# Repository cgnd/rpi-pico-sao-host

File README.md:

---
typora-copy-images-to: ./images
---

# Raspberry Pi Pico SAO Host

The [Raspberry Pi Pico SAO Host](https://github.com/cgnd/rpi-pico-sao-host) is a breakout board that adds [Simple Add-on (SAO)](https://hackaday.io/project/175182-simple-add-ons-sao) host connectors to the [Raspberry Pi Pico](https://www.raspberrypi.com/products/raspberry-pi-pico/).

## v2 Design (latest)

The `v2` design adds the following features:

* A power switch (`SW2`) attached to the the Pico's `3V3_EN` input pin.
* A power LED (`D1`) that turns on when the Pico is powered on.
* A tactile reset switch (`SW1`) connected to the Pico's `RUN` input pin.

See the [CHANGELOG](CHANGELOG.md) for a full list of the changes from the previous version.

**Top (Primary) Side**

**Bottom (Secondary) Side**

### Checking out the design

To check out the design, [download the zip](https://github.com/cgnd/rpi-pico-sao-host/archive/refs/heads/v2.zip) or clone the repository using Git.

```sh
git clone https://github.com/cgnd/rpi-pico-sao-host.git
```

Open the the [RPi_Pico_SAO_Host.kicad_pro](RPi_Pico_SAO_Host.kicad_pro) project file in KiCad (requires version 9 or later).

## v1 Design

See the [README](https://github.com/cgnd/rpi-pico-sao-host/blob/v1/README.md) on the [v1](https://github.com/cgnd/rpi-pico-sao-host/tree/v1) branch for information about the `v1` design.

## License

See the [LICENSE](LICENSE.md) file for copyright & license information.

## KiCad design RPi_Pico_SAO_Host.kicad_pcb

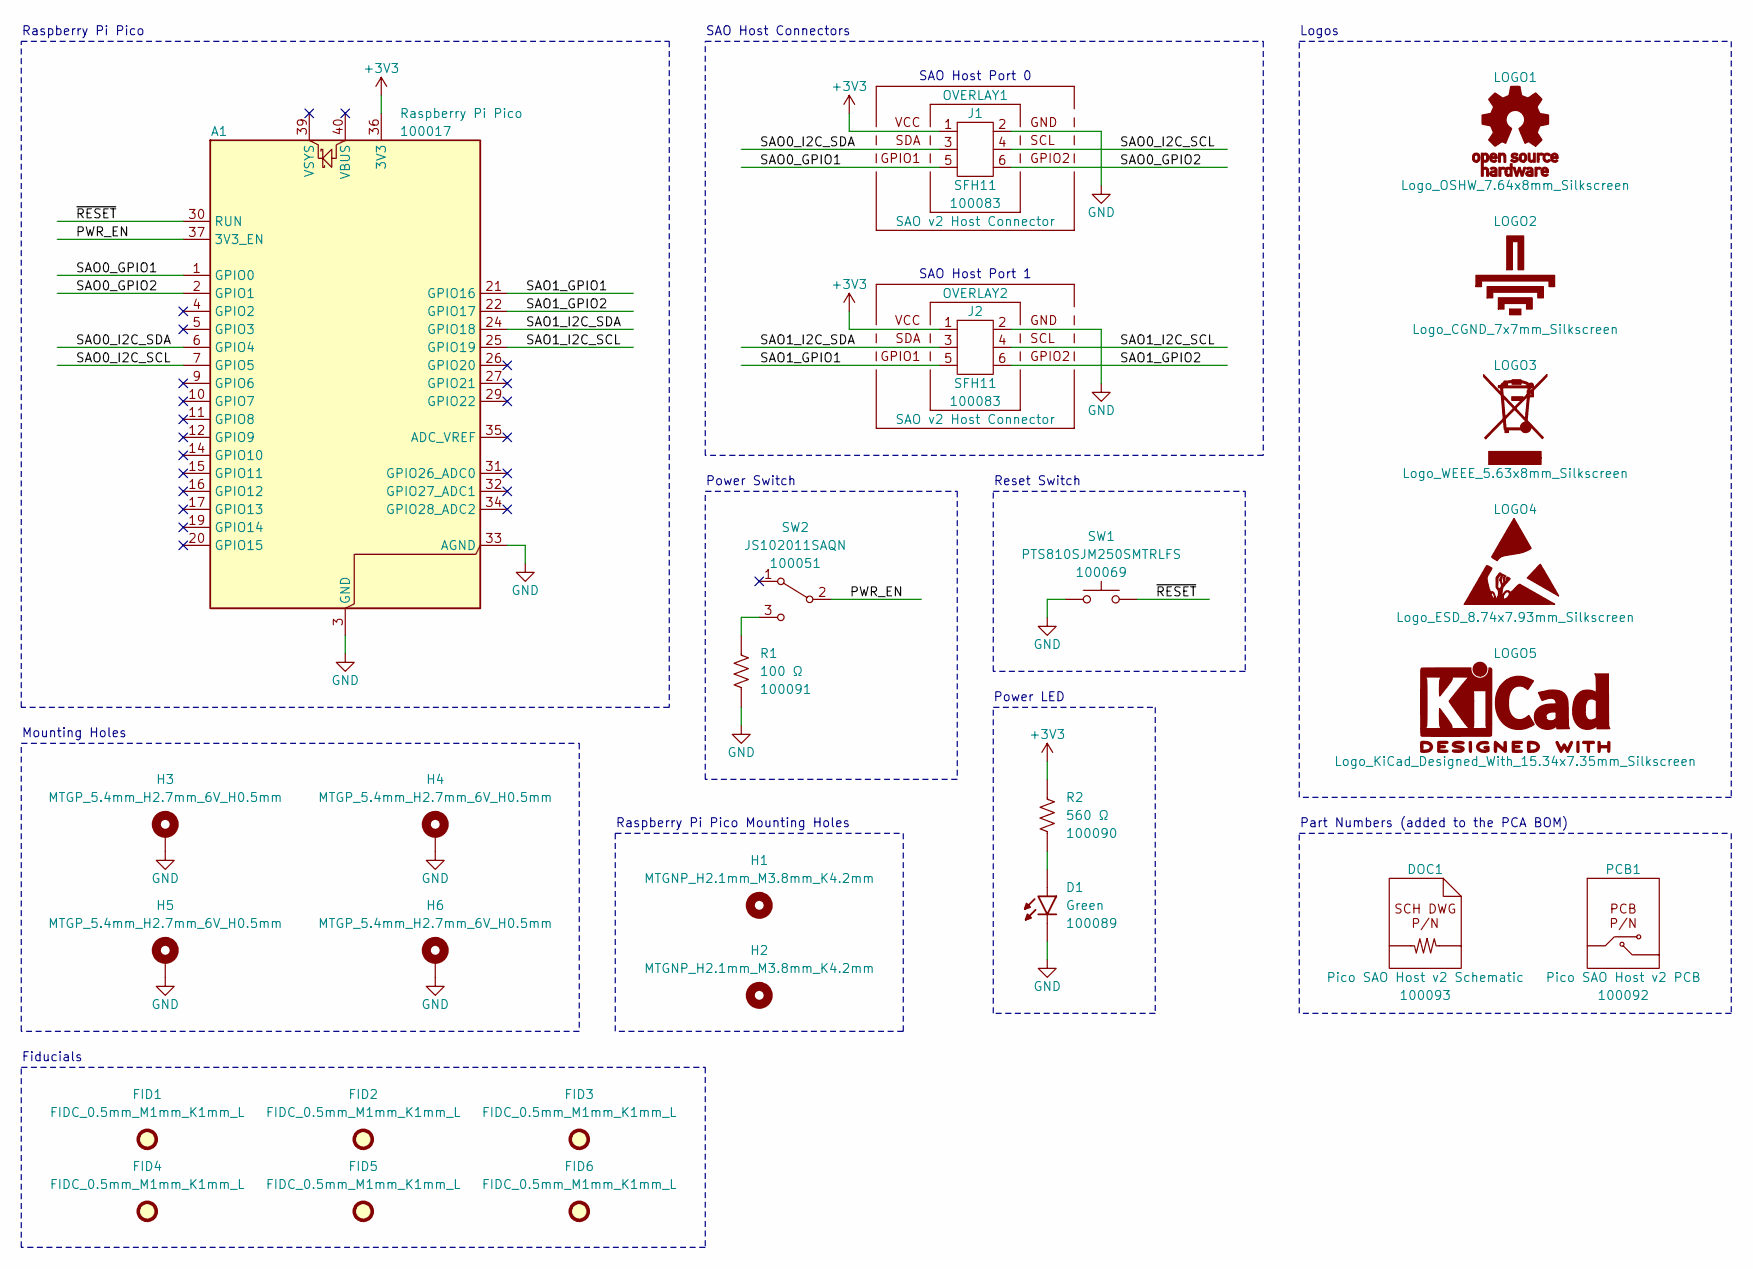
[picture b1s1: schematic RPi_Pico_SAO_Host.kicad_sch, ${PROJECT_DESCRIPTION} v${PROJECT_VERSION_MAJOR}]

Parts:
A1: Raspberry Pi Pico; Raspberry_Pi_Pico_Common_SMD
D1: Green; LEDSC_0603_0.8x1.6x0.8mm_L0.45x0.7mm_N
DOC1: Pico SAO Host v2 Schematic
FID1, FID2, FID3, FID4, FID5, FID6: FIDC_0.5mm_M1mm_K1mm_L
H1, H2: MTGNP_H2.1mm_M3.8mm_K4.2mm
H3, H4, H5, H6: MTGP_5.4mm_H2.7mm_6V_H0.5mm
J1, J2: SFH11; Sullins_SFH11-xxxC-D03-ST-BK
LOGO1: Logo_OSHW_7.64x8mm_Silkscreen
LOGO2: Logo_CGND_7x7mm_Silkscreen
LOGO3: Logo_WEEE_5.63x8mm_Silkscreen
LOGO4: Logo_ESD_8.74x7.93mm_Silkscreen
LOGO5: Logo_KiCad_Designed_With_15.34x7.35mm_Silkscreen
OVERLAY1, OVERLAY2: SAO v2 Host Connector; Overlay_SAO_v2_Host
PCB1: Pico SAO Host v2 PCB
R1: 100 Ω; RESC_0603_1.6x0.8x0.55mm_L0.25mm_N
R2: 560 Ω; RESC_0603_1.6x0.8x0.55mm_L0.25mm_N
SW1: PTS810SJM250SMTRLFS; CK_PTS810SJx250
SW2: JS102011SAQN; CK_JS102011SAxN

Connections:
+3V3: A1.36 (3V3), J1.1, J2.1, R2.1
/PWR_EN: A1.37 (3V3_EN), SW2.2 (B)
/SAO0_GPIO1: A1.1 (GPIO0), J1.5
/SAO0_GPIO2: A1.2 (GPIO1), J1.6
/SAO0_I2C_SCL: A1.7 (GPIO5), J1.4
/SAO0_I2C_SDA: A1.6 (GPIO4), J1.3
/SAO1_GPIO1: A1.21 (GPIO16), J2.5
/SAO1_GPIO2: A1.22 (GPIO17), J2.6
/SAO1_I2C_SCL: A1.25 (GPIO19), J2.4
/SAO1_I2C_SDA: A1.24 (GPIO18), J2.3
/~RESET: A1.30 (RUN), SW1.2
GND: A1.3 (GND), A1.8 (GND), A1.13 (GND), A1.18 (GND), A1.23 (GND), A1.28 (GND), A1.33 (AGND), A1.38 (GND), D1.C (Cathode), H3.1, H4.1, H5.1, H6.1, J1.2, J2.2, R1.2, SW1.1
unnamed: D1.A (Anode), R2.2
unnamed: R1.1, SW2.3 (C)

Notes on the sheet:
Fiducials
SAO Host Port 0
Mounting Holes
Part Numbers (added to the PCA BOM)
Power Switch
Logos
Power LED
SAO Host Port 1
Raspberry Pi Pico Mounting Holes
Reset Switch
SAO Host Connectors
Raspberry Pi Pico

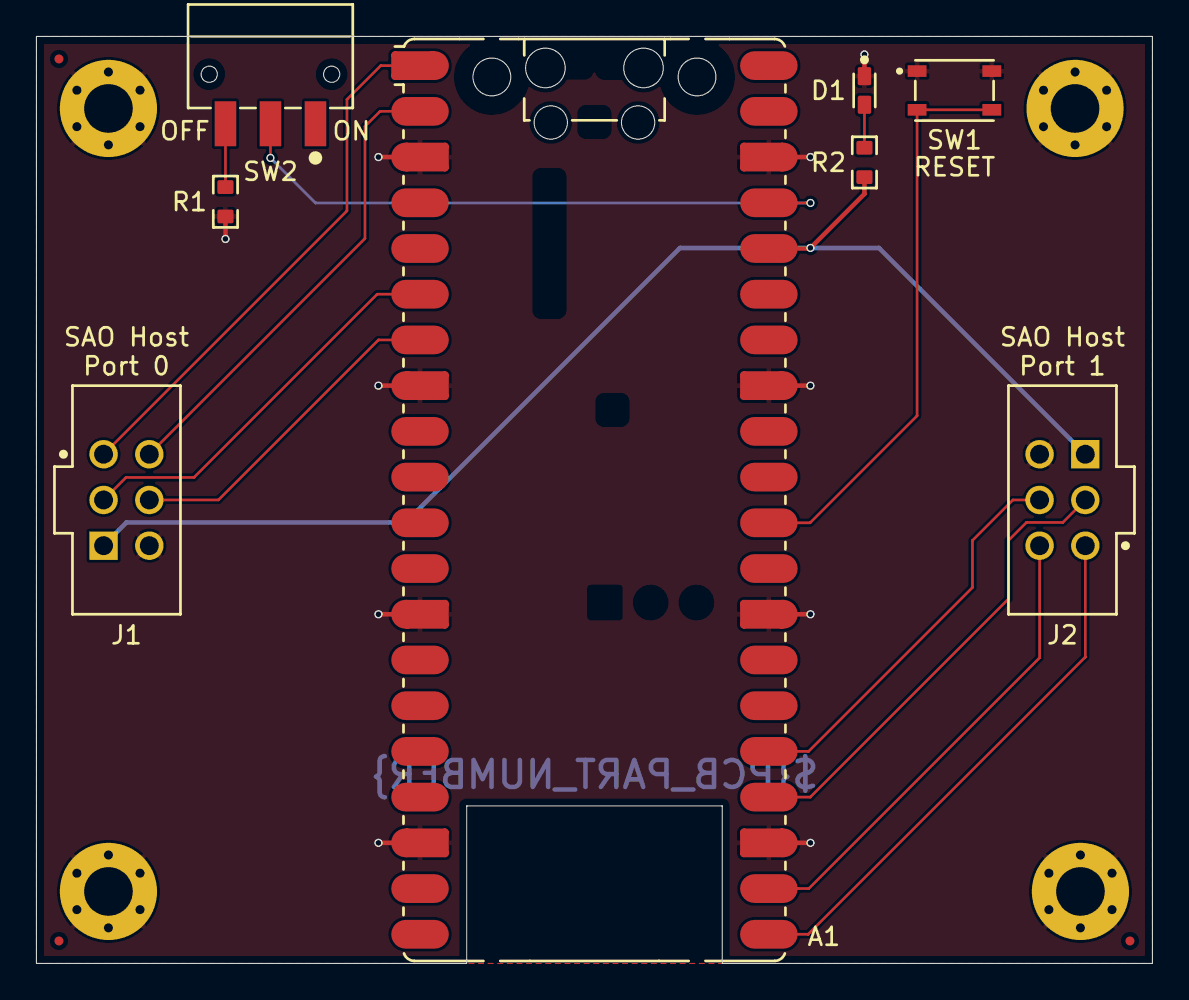
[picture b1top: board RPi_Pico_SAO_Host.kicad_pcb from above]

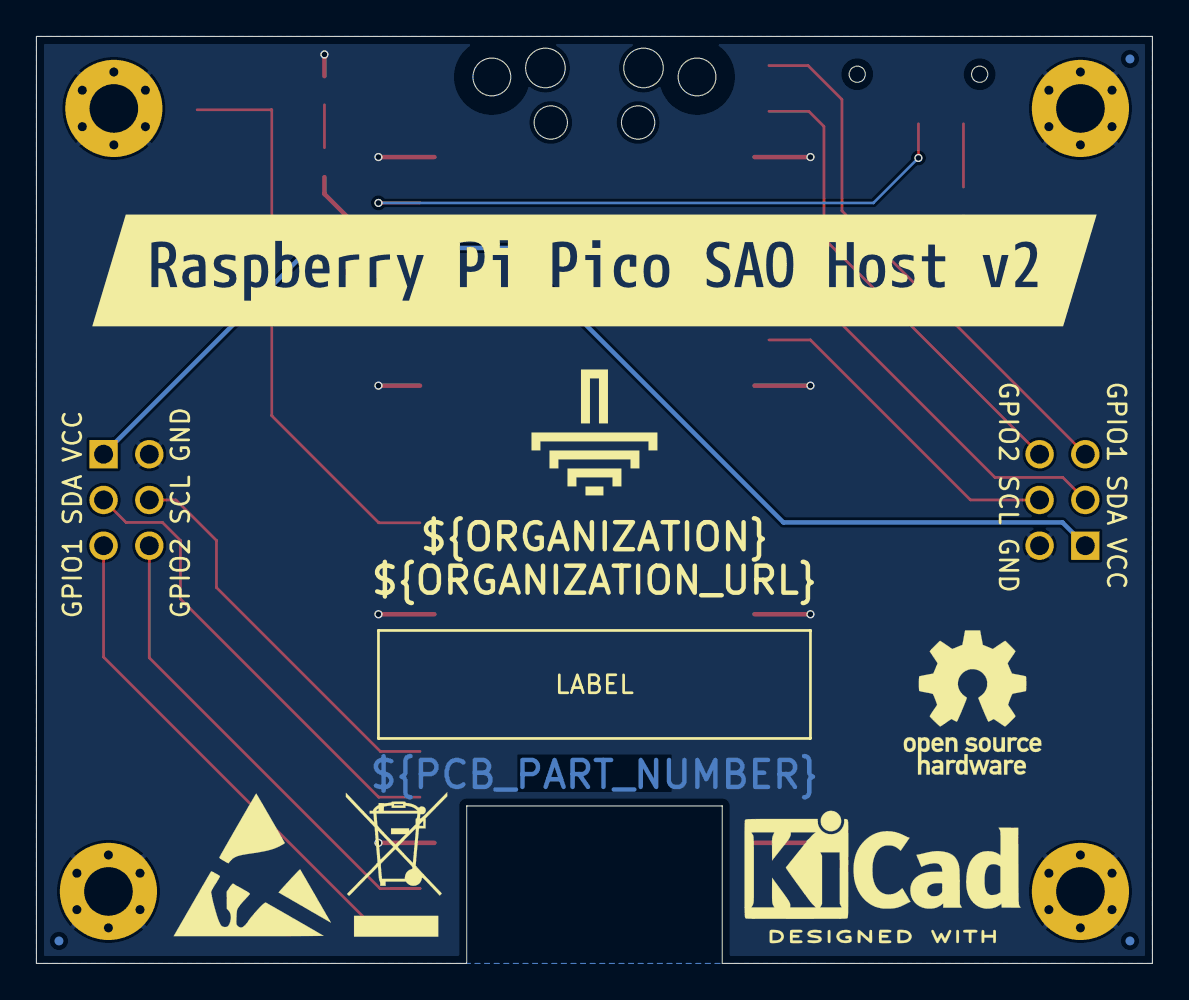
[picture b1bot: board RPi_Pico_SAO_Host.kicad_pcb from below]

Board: 2 copper layers, 62.0 x 51.5 mm, 28 parts (9 on the bottom side), 14 nets.

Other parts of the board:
kibuzzard-68151D09: VAL**; kibuzzard-68151D09

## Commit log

2024-10-15 Add 100081 Rev 1 schematic and layout
2024-10-15 Update output settings
2024-10-15 Update schematic export settings
2024-10-26 Add incompatibility note to README for Pico W
2024-10-26 Add Typora image dir front matter to README
2025-05-04 Update v1 project layout and revision scheme
2025-05-04 Add a changelog
2025-05-04 Fix issue date in PCB title block
2025-05-04 Add pre-commit and license info
2025-05-04 Move license info into a dedicated file
2025-05-04 Fix typo in README
2025-05-04 Update notes in the README
2025-05-09 Add v2 design changes
2025-05-09 Fix v2.0.0 release date in the CHANGELOG
2025-05-12 Fix layer types for F.Fab and B.Fab layers
2025-05-12 Fix missing layers in kicad-cli exports
2025-05-12 Add mounting hole outlines on Fab layers
2025-05-12 Add mounting hole outlines to Assembly layers
2025-05-12 Update CHANGELOG for 2.0.1 release
2025-05-12 Change PCB revision to 'B'
2025-05-15 Remove old copyright & license fields
2025-05-16 Clean up KiCad project file
2025-05-16 Remove hard-coded project metadata from tasks.py
2025-05-17 Remove old library setup instructions from CONTRIBUTING.md
2025-05-23 Update CGND_OSHW_IPN library URI
2025-05-23 Remove Symbol field from symbols and footprints
2025-05-23 Update cgnd-kicad-lib

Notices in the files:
RPi_Pico_SAO_Host.kicad_pcb:
License: ${SPDX_LICENSE_ID}
Copyright: © ${COPYRIGHT_HOLDER}
parts and their libraries:
SPDX_LICENSE_ID: CERN-OHL-P-2.0
